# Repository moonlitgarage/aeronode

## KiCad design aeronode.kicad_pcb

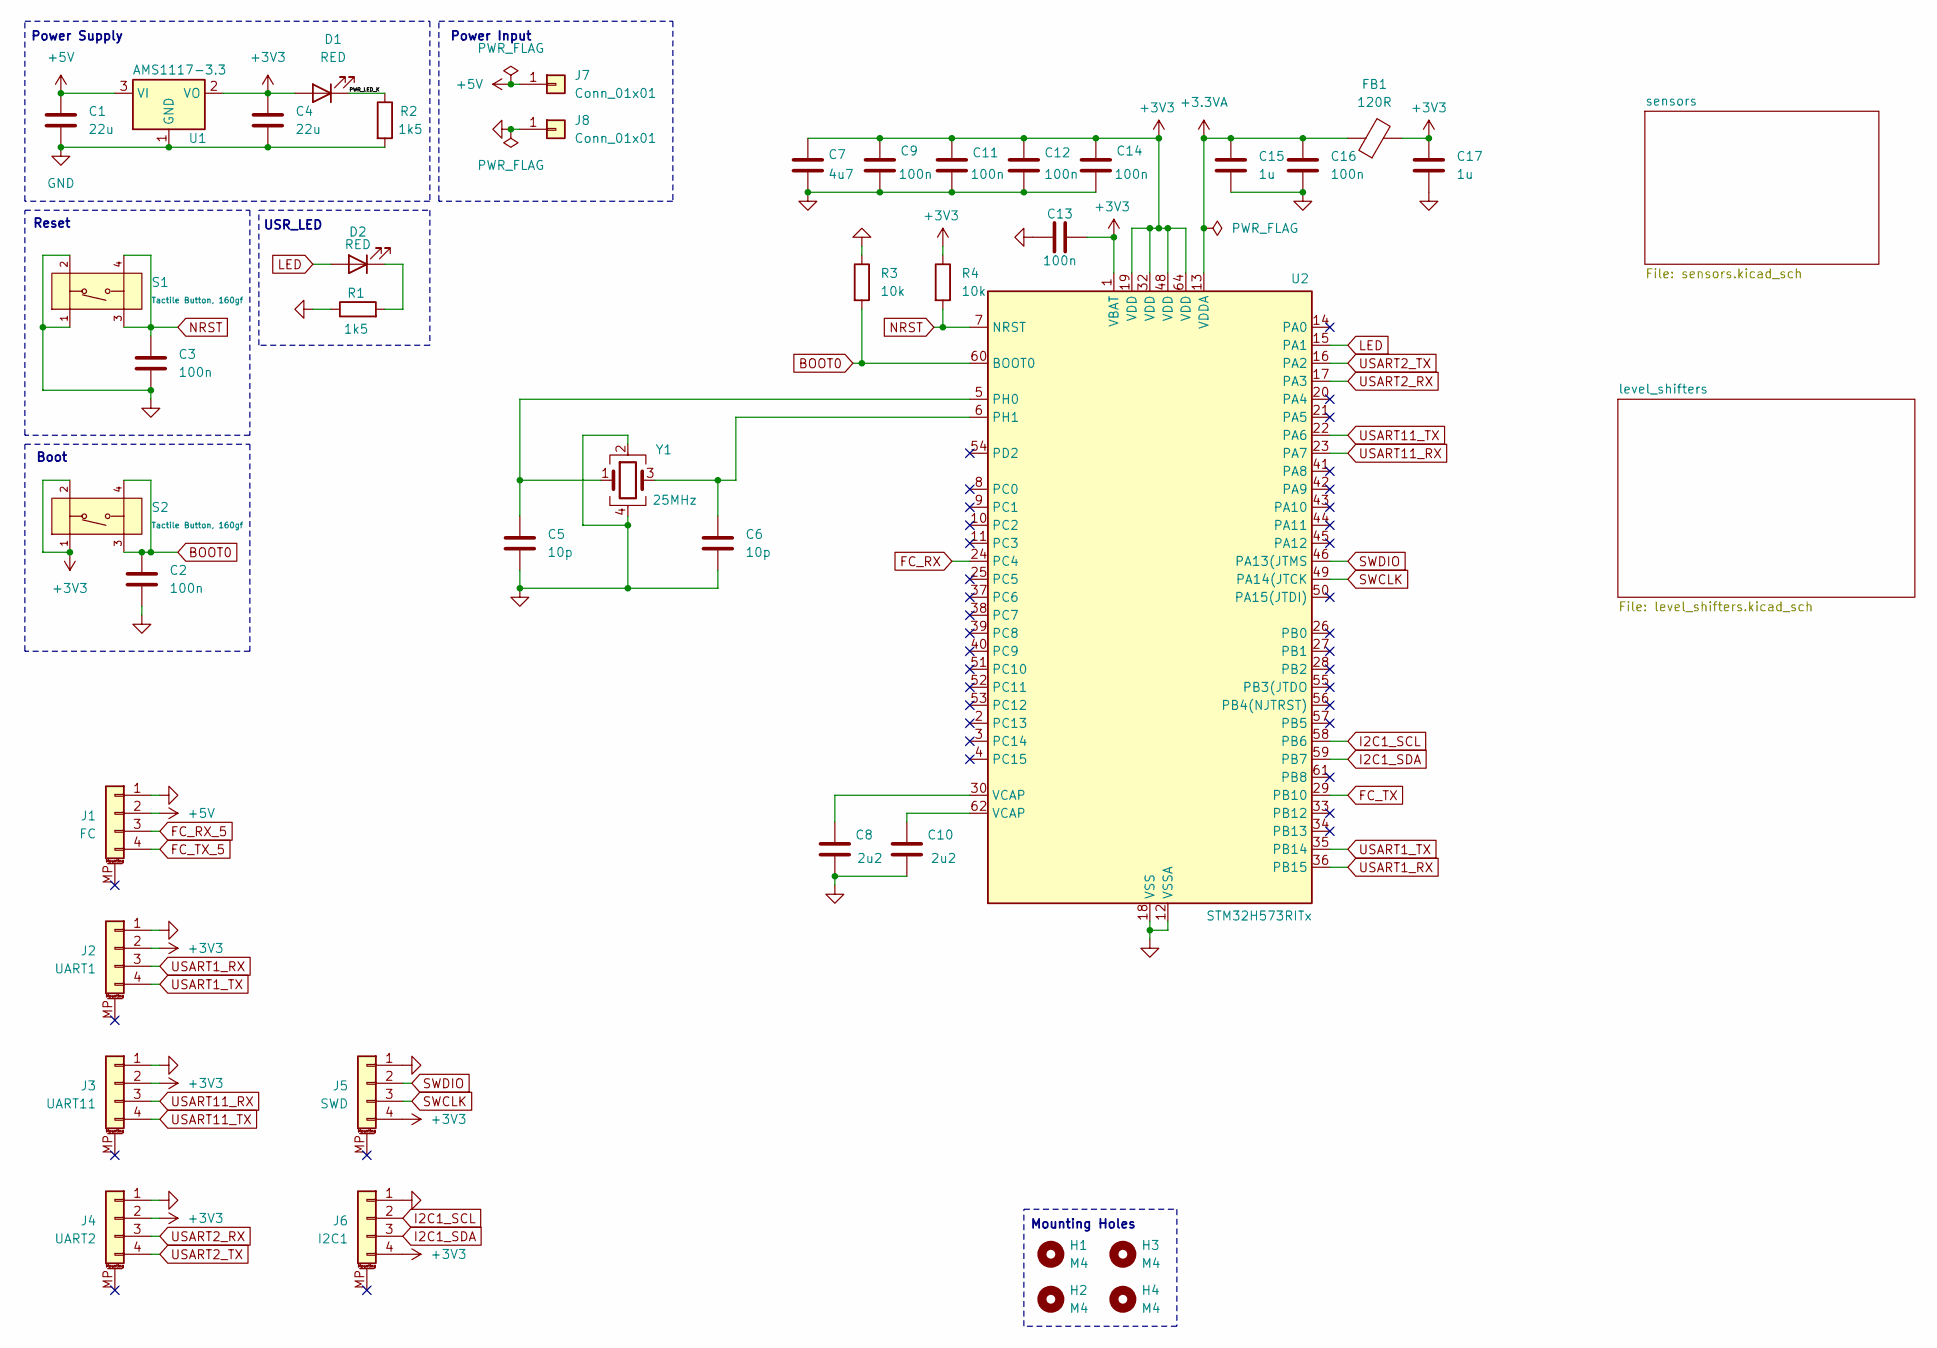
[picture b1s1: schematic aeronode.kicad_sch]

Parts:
C1, C4: 22u; C_0805_2012Metric
C2, C3, C9, C11, C12, C13, C14, C16: 100n; C_0402_1005Metric
C5, C6: 10p; C_0402_1005Metric
C7: 4u7; C_0603_1608Metric
C8, C10: 2u2; C_0402_1005Metric
C15, C17: 1u; C_0402_1005Metric
D1, D2: RED; LED_0603_1608Metric
FB1: 120R; L_0603_1608Metric
H1, H2, H3, H4: M4; MountingHole_4.3mm_M4
J1: FC; JST_GH_SM04B-GHS-TB_1x04-1MP_P1.25mm_Horizontal
J2: UART1; JST_GH_SM04B-GHS-TB_1x04-1MP_P1.25mm_Horizontal
J3: UART11; JST_GH_SM04B-GHS-TB_1x04-1MP_P1.25mm_Horizontal
J4: UART2; JST_GH_SM04B-GHS-TB_1x04-1MP_P1.25mm_Horizontal
J5: SWD; JST_GH_SM04B-GHS-TB_1x04-1MP_P1.25mm_Horizontal
J6: I2C1; JST_GH_SM04B-GHS-TB_1x04-1MP_P1.25mm_Horizontal
J7, J8: Conn_01x01; SolderWirePad_1x01_SMD_2x4mm
R1, R2: 1k5; R_0402_1005Metric
R3, R4: 10k; R_0402_1005Metric
S1, S2: Tactile Button, 160gf; SW-SMD_4P-L5.1-W5.1-P3.70-LS6.5-TL-2; Voltage Rating (Dc) 12V; Part TS-1187A-B-A-B; LCSC C318884
U1: AMS1117-3.3; SOT-223-3_TabPin2
U2: STM32H573RITx; LQFP-64_10x10mm_P0.5mm
Y1: 25MHz; Crystal_SMD_3225-4Pin_3.2x2.5mm

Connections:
+3.3VA: C15.2, C16.2, FB1.1, U2.13 (VDDA)
+3V3: C4.1, C7.1, C9.1, C11.1, C12.1, C13.2, C14.1, C17.2, D1.2 (A), FB1.2, J2.2, J3.2, J4.2, J5.4, J6.4, R4.1, S2.1 (A), S2.2 (B), U1.2 (VO), U2.1 (VBAT), U2.19 (VDD), U2.32 (VDD), U2.48 (VDD), U2.64 (VDD); also elsewhere on the board
+5V: C1.1, J1.2, J7.1, U1.3 (VI); also elsewhere on the board
/PWR_LED_K: D1.1 (K), R2.1
BOOT0: C2.1, R3.2, S2.3 (C), S2.4 (D), U2.60 (BOOT0)
FC_RX: U2.24 (PC4); also elsewhere on the board
FC_RX_5: J1.3; also elsewhere on the board
FC_TX: U2.29 (PB10); also elsewhere on the board
FC_TX_5: J1.4; also elsewhere on the board
GND: C1.2, C2.2, C3.2, C4.2, C5.2, C6.2, C7.2, C8.2, C9.2, C10.2, C11.2, C12.2, C13.1, C14.2, C15.1, C16.1, C17.1, J1.1, J2.1, J3.1, J4.1, J5.1, J6.1, J8.1, R1.1, R2.2, R3.1, S1.1 (A), S1.2 (B), U1.1 (GND), U2.12 (VSSA), U2.18 (VSS), U2.31 (VSS), U2.47 (VSS), U2.63 (VSS), Y1.2, Y1.4; also elsewhere on the board
I2C1_SCL: J6.2, U2.58 (PB6); also elsewhere on the board
I2C1_SDA: J6.3, U2.59 (PB7); also elsewhere on the board
LED: D2.2 (A), U2.15 (PA1)
NRST: C3.1, R4.2, S1.3 (C), S1.4 (D), U2.7 (NRST)
unnamed: C8.1, U2.30 (VCAP)
unnamed: C10.1, U2.62 (VCAP)
unnamed: D2.1 (K), R1.2
unnamed: C5.1, U2.5 (PH0), Y1.1
unnamed: C6.1, U2.6 (PH1), Y1.3
SWCLK: J5.3, U2.49 (PA14(JTCK)
SWDIO: J5.2, U2.46 (PA13(JTMS)
USART1_RX: J2.3, U2.36 (PB15)
USART1_TX: J2.4, U2.35 (PB14)
USART2_RX: J4.3, U2.17 (PA3)
USART2_TX: J4.4, U2.16 (PA2)
USART11_RX: J3.3, U2.23 (PA7)
USART11_TX: J3.4, U2.22 (PA6)

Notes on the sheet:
Power Input
Power Supply
USR_LED
Mounting Holes
Reset
Boot

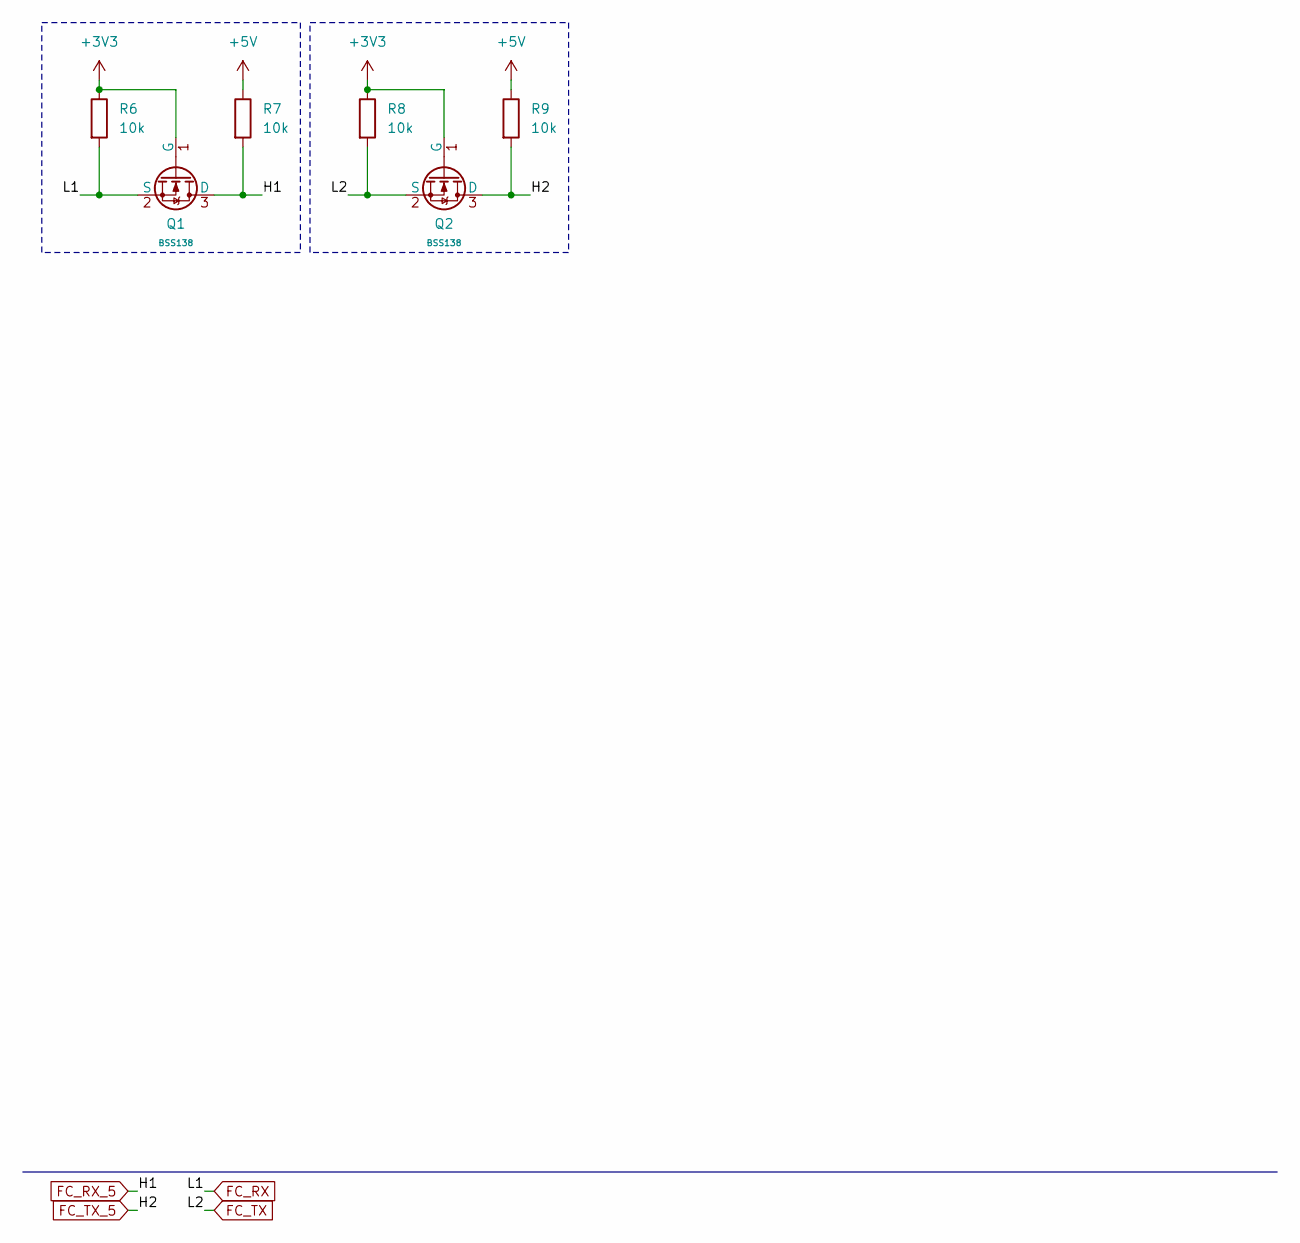
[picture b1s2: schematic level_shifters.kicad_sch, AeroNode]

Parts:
Q1, Q2: BSS138; Q_SOT-23; Part BSS138; LCSC C7420339
R6, R7, R8, R9: 10k; R_0402_1005Metric

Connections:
+3V3: Q1.1 (G), Q2.1 (G), R6.1, R8.1; also elsewhere on the board
+5V: R7.1, R9.1; also elsewhere on the board
FC_RX: Q1.2 (S), R6.2; also elsewhere on the board
FC_RX_5: Q1.3 (D), R7.2; also elsewhere on the board
FC_TX: Q2.2 (S), R8.2; also elsewhere on the board
FC_TX_5: Q2.3 (D), R9.2; also elsewhere on the board

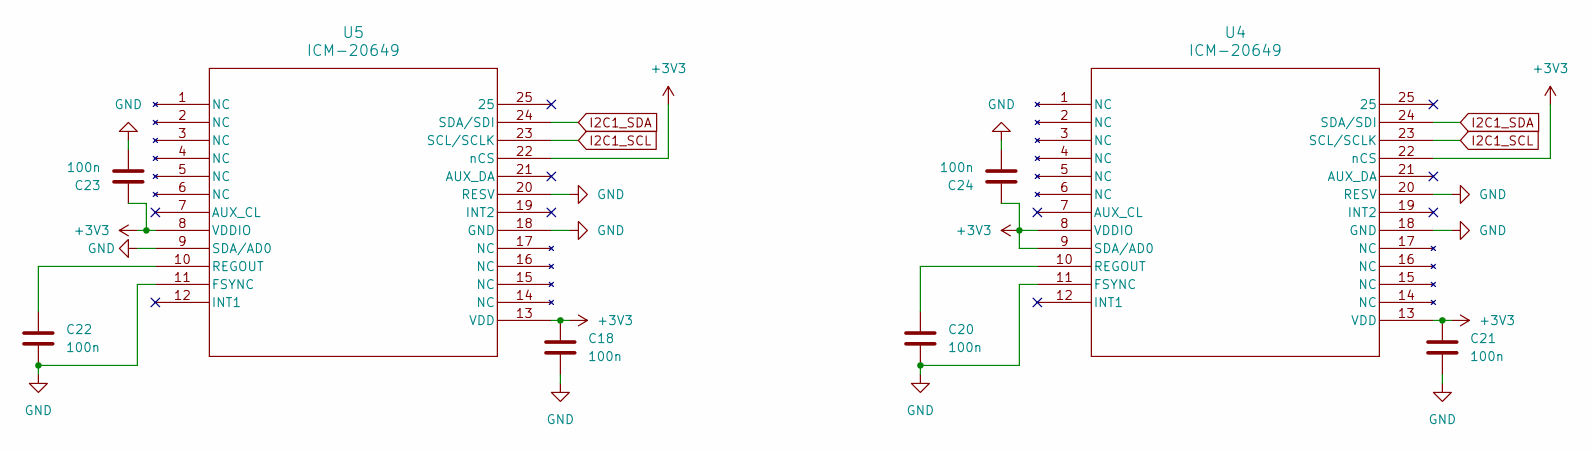
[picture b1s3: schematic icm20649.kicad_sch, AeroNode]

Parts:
C18, C20, C21, C22, C23, C24: 100n; C_0402_1005Metric
U4, U5: ICM-20649; QFN24_3X3X0P9_IVS

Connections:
+3V3: C18.1, C21.1, C23.1, C24.1, U4.8 (VDDIO), U4.9 (SDA/AD0), U4.13 (VDD), U4.22 (nCS), U5.8 (VDDIO), U5.13 (VDD), U5.22 (nCS); also elsewhere on the board
GND: C18.2, C20.2, C21.2, C22.2, C23.2, C24.2, U4.11 (FSYNC), U4.18 (GND), U4.20 (RESV), U5.9 (SDA/AD0), U5.11 (FSYNC), U5.18 (GND), U5.20 (RESV); also elsewhere on the board
I2C1_SCL: U4.23 (SCL/SCLK), U5.23 (SCL/SCLK); also elsewhere on the board
I2C1_SDA: U4.24 (SDA/SDI), U5.24 (SDA/SDI); also elsewhere on the board
unnamed: C20.1, U4.10 (REGOUT)
unnamed: C22.1, U5.10 (REGOUT)

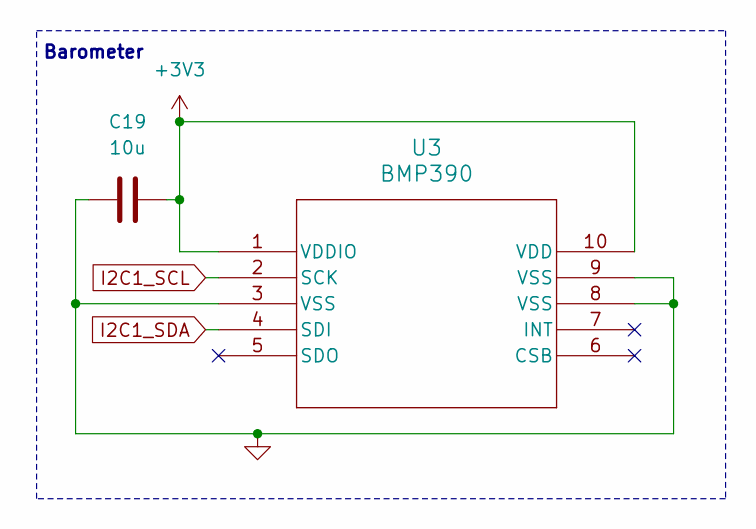
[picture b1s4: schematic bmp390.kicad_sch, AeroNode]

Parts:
C19: 10u; C_0402_1005Metric
U3: BMP390; 10LGA_2X2X0p75_BOS

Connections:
+3V3: C19.1, U3.1 (VDDIO), U3.10 (VDD); also elsewhere on the board
GND: C19.2, U3.3 (VSS), U3.8 (VSS), U3.9 (VSS); also elsewhere on the board
I2C1_SCL: U3.2 (SCK); also elsewhere on the board
I2C1_SDA: U3.4 (SDI); also elsewhere on the board

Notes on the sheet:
Barometer

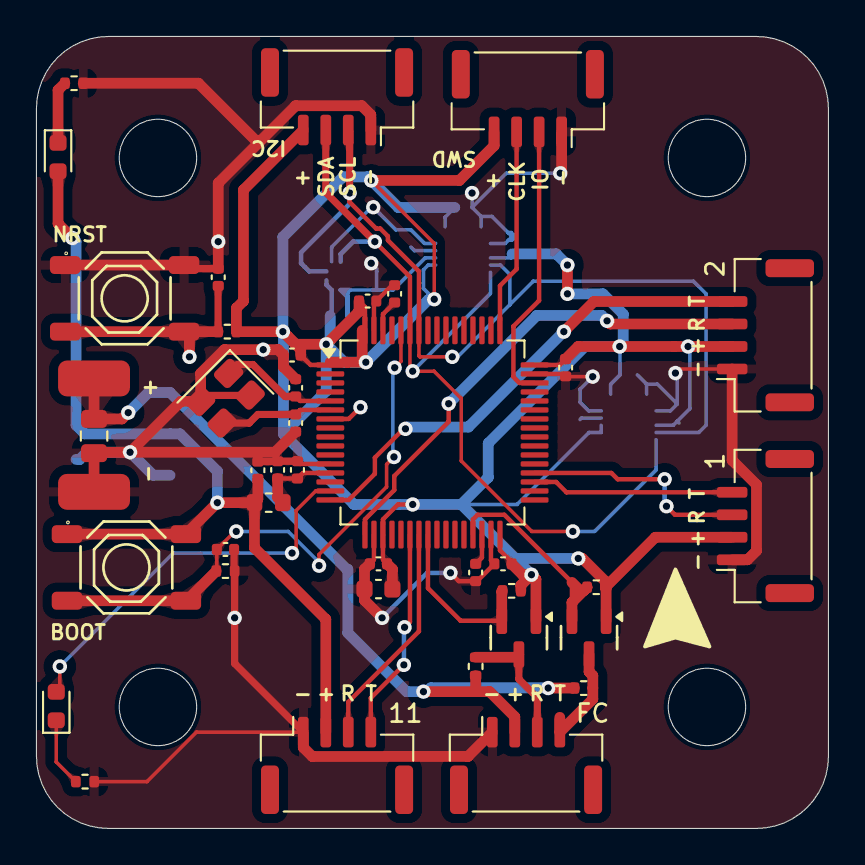
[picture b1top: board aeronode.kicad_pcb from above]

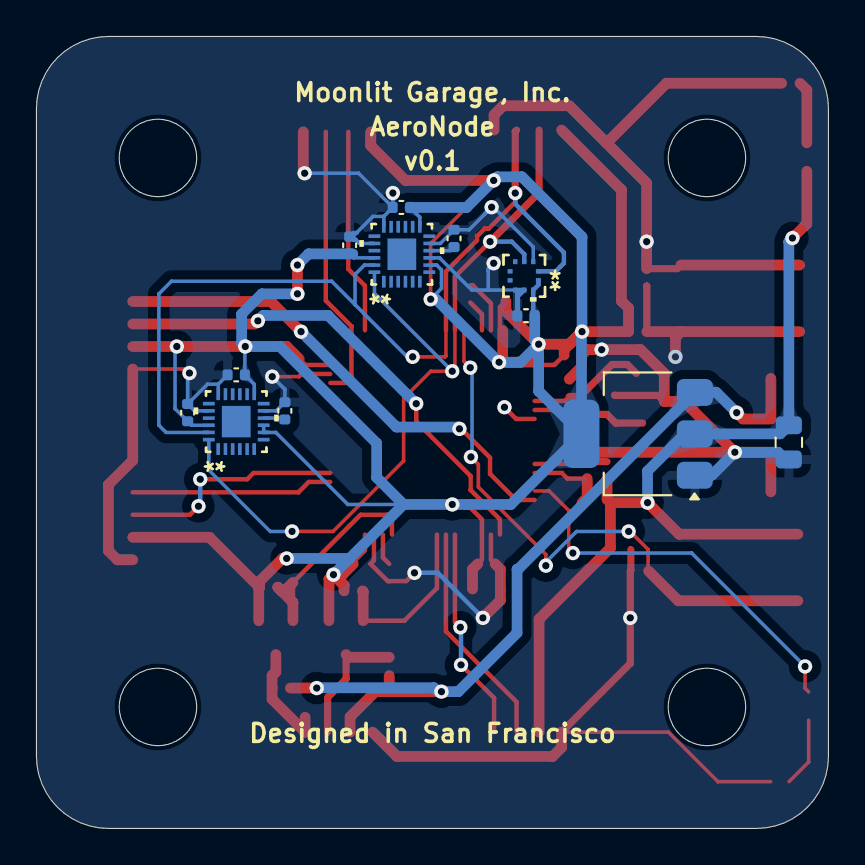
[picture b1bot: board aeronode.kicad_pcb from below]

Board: 4 copper layers, 44.0 x 44.0 mm, 57 parts (12 on the bottom side), 29 nets.

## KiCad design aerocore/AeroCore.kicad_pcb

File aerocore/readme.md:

# aerocore
## components
| Type | ID | I2C | SPI | Datasheet | Product Link | Optional |
| :---: | :---: | :---: | :---: | :---: | :---: | :---: |
| Accel + Gyro | BMI088 | Y | Y | [mouser](https://www.mouser.com/datasheet/2/783/BST_BMI088_DS001-1509549.pdf) | [mouser](https://www.mouser.com/ProductDetail/262-BMI088) | N |
| Magnetometer | LIS3MDLTR | Y | Y | [mouser](https://www.mouser.com/datasheet/2/389/lis3mdl-1849592.pdf) | [mouser](https://www.mouser.com/ProductDetail/STMicroelectronics/LIS3MDLTR?qs=hnsWAVXnr6EbLE48dGN9Pg%3D%3D) | N |
| Pressure + Temp | BMP390 | Y | Y | [mouser](https://www.mouser.com/datasheet/2/783/bst_bmp390_ds002-2448819.pdf) | [mouser](https://www.mouser.com/ProductDetail/Bosch-Sensortec/BMP390?qs=QNEnbhJQKvYQVfvRMgo2YA%3D%3D) | N |
| LoRa | RFM95W | - | Y | [mouser](https://www.mouser.com/datasheet/2/975/1463993415RFM95_96_97_98W-1858106.pdf) / [hoperf](https://www.hoperf.com/uploads/RFM96W-V2.0_1695351477.pdf) | [mouser](https://www.mouser.com/ProductDetail/RF-Solutions/RFM95W-868S2?qs=sGAEpiMZZMu3sxpa5v1qriuzrjO9DfPi5Wv3OoHC154%3D) | Y |
| MCU | RP2040  | - | - | [raspberrypi](https://datasheets.raspberrypi.com/rp2040/rp2040-datasheet.pdf) | [raspberrypi](https://www.raspberrypi.com/documentation/microcontrollers/rp2040.html) | N |

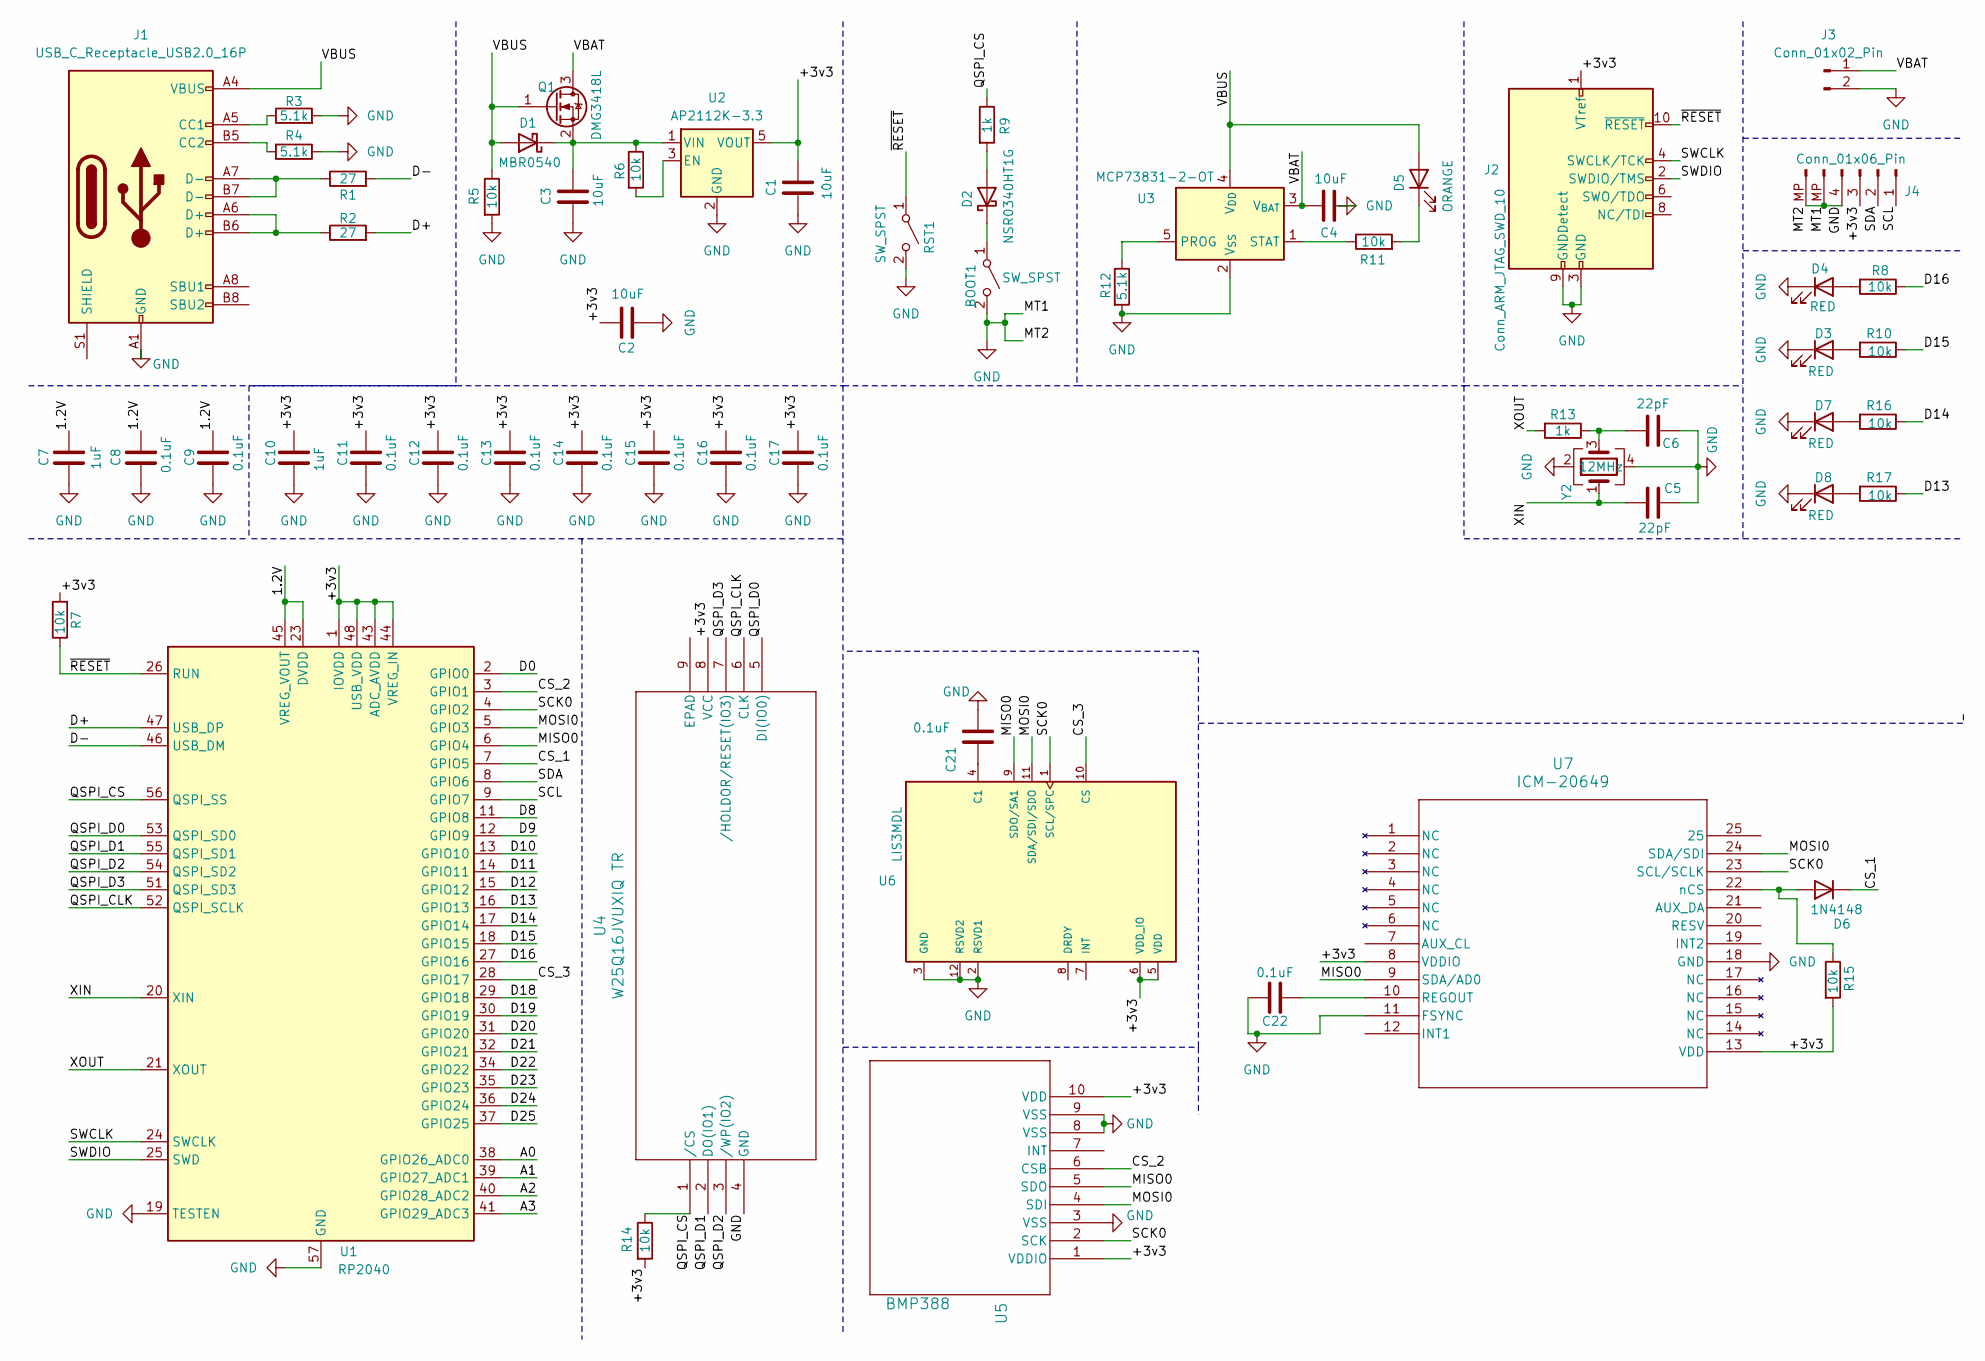
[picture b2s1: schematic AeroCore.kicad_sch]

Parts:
BOOT1: SW_SPST; SW_Push_1P1T_NO_CK_KMR2
C1, C2, C3, C4: 10uF; C_0805_2012Metric_Pad1.18x1.45mm_HandSolder
C5, C6: 22pF; C_0805_2012Metric_Pad1.18x1.45mm_HandSolder
C7, C10: 1uF; C_0603_1608Metric_Pad1.08x0.95mm_HandSolder
C8, C9, C11, C12, C13, C14, C15, C16, C17, C21, C22: 0.1uF; C_0603_1608Metric_Pad1.08x0.95mm_HandSolder
D1: MBR0540; D_SOD-123
D2: NSR0340HT1G; D_SOD-323
D3, D4, D7, D8: RED; LED_0603_1608Metric_Pad1.05x0.95mm_HandSolder
D5: ORANGE; LED_0603_1608Metric_Pad1.05x0.95mm_HandSolder
D6: 1N4148; D_DO-35_SOD27_P7.62mm_Horizontal
J1: USB_C_Receptacle_USB2.0_16P; USB_C_Receptacle_Palconn_UTC16-G
J2: Conn_ARM_JTAG_SWD_10; PinSocket_2x05_P1.27mm_Vertical_SMD
J3: Conn_01x02_Pin; JST_EH_S2B-EH_1x02_P2.50mm_Horizontal
J4: Conn_01x06_Pin; JST_SH_SM04B-SRSS-TB_1x04-1MP_P1.00mm_Horizontal
Q1: DMG3418L; SOT-23
R1, R2: 27; R_0603_1608Metric_Pad0.98x0.95mm_HandSolder
R3, R4, R12: 5.1k; R_0603_1608Metric_Pad0.98x0.95mm_HandSolder
R5, R6, R7, R8, R10, R11, R14, R15, R16, R17: 10k; R_0603_1608Metric_Pad0.98x0.95mm_HandSolder
R9, R13: 1k; R_0603_1608Metric_Pad0.98x0.95mm_HandSolder
RST1: SW_SPST; SW_Push_1P1T_NO_CK_KMR2
U1: RP2040; QFN-56-1EP_7x7mm_P0.4mm_EP3.2x3.2mm
U2: AP2112K-3.3; SOT-23-5
U3: MCP73831-2-OT; SOT-23-5
U4: W25Q16JVUXIQ TR; Winbond_USON-8-1EP_3x2mm_P0.5mm_EP0.2x1.6mm
U5: BMP388; SENSORM-SMD_BMP388
U6: LIS3MDL; LGA-12_L2.0-W2.0-P0.50-BL; PARTREV 6
U7: ICM-20649; QFN-24_L3.0-W3.0-P0.40-TL-EP1.4
Y2: 12MHz; Crystal_SMD_2520-4Pin_2.5x2.0mm

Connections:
/1.2V: C7.1, C8.1, C9.1, U1.23 (DVDD), U1.45 (VREG_VOUT), U1.50 (DVDD)
/+3v3: C1.1, C2.1, C10.1, C11.1, C12.1, C13.1, C14.1, C15.1, C16.1, C17.1, J2.1 (VTref), J4.3, R7.2, R14.2, R15.2, U1.1 (IOVDD), U1.10 (IOVDD), U1.22 (IOVDD), U1.33 (IOVDD), U1.42 (IOVDD), U1.43 (ADC_AVDD), U1.44 (VREG_IN), U1.48 (USB_VDD), U1.49 (IOVDD), U2.5 (VOUT), U4.8 (VCC), U5.1 (VDDIO), U5.10 (VDD), U6.5 (VDD), U6.6 (VDD_IO), U7.8 (VDDIO), U7.13 (VDD)
/A0: U1.38 (GPIO26_ADC0)
/A1: U1.39 (GPIO27_ADC1)
/A2: U1.40 (GPIO28_ADC2)
/A3: U1.41 (GPIO29_ADC3)
/CS_1: D6.1 (K), U1.7 (GPIO5)
/CS_2: U1.3 (GPIO1), U5.6 (CSB)
/CS_3: U1.28 (GPIO17), U6.10 (CS)
/D0: U1.2 (GPIO0)
/D8: U1.11 (GPIO8)
/D9: U1.12 (GPIO9)
/D10: U1.13 (GPIO10)
/D11: U1.14 (GPIO11)
/D12: U1.15 (GPIO12)
/D13: R17.1, U1.16 (GPIO13)
/D14: R16.1, U1.17 (GPIO14)
/D15: R10.1, U1.18 (GPIO15)
/D16: R8.1, U1.27 (GPIO16)
/D18: U1.29 (GPIO18)
/D19: U1.30 (GPIO19)
/D20: U1.31 (GPIO20)
/D21: U1.32 (GPIO21)
/D22: U1.34 (GPIO22)
/D23: U1.35 (GPIO23)
/D24: U1.36 (GPIO24)
/D25: U1.37 (GPIO25)
/D+: R2.2, U1.47 (USB_DP)
/D-: R1.2, U1.46 (USB_DM)
/MISO0: U1.6 (GPIO4), U5.5 (SDO), U6.9 (SDO/SA1), U7.9 (SDA/AD0)
/MOSI0: U1.5 (GPIO3), U5.4 (SDI), U6.11 (SDA/SDI/SDO), U7.24 (SDA/SDI)
/QSPI_CLK: U1.52 (QSPI_SCLK), U4.6 (CLK)
/QSPI_CS: R9.1, R14.1, U1.56 (QSPI_SS), U4.1 (/CS)
/QSPI_D0: U1.53 (QSPI_SD0), U4.5 (DI(IO0))
/QSPI_D1: U1.55 (QSPI_SD1), U4.2 (DO(IO1))
/QSPI_D2: U1.54 (QSPI_SD2), U4.3 (/WP(IO2))
/QSPI_D3: U1.51 (QSPI_SD3), U4.7 (/HOLDOR/RESET(IO3))
/SCK0: U1.4 (GPIO2), U5.2 (SCK), U6.1 (SCL/SPC), U7.23 (SCL/SCLK)
/SCL: J4.1, U1.9 (GPIO7)
/SDA: J4.2, U1.8 (GPIO6)
/SWCLK: J2.4 (SWCLK/TCK), U1.24 (SWCLK)
/SWDIO: J2.2 (SWDIO/TMS), U1.25 (SWD)
/VBAT: C4.1, J3.1, Q1.3 (D), U3.3 (V_{BAT})
/VBUS: D1.2 (A), D5.2 (A), J1.A4 (VBUS), J1.A9 (VBUS), J1.B4 (VBUS), J1.B9 (VBUS), Q1.1 (G), R5.1, U3.4 (V_{DD})
/XIN: C5.2, U1.20 (XIN), Y2.1
/XOUT: R13.2, U1.21 (XOUT)
/~RESET: J2.10 (~RESET), R7.1, RST1.1 (A), U1.26 (RUN)
GND: BOOT1.2 (B), C1.2, C2.2, C3.2, C4.2, C5.1, C6.1, C7.2, C8.2, C9.2, C10.2, C11.2, C12.2, C13.2, C14.2, C15.2, C16.2, C17.2, C21.2, C22.1, D3.1 (K), D4.1 (K), D7.1 (K), D8.1 (K), J1.A1 (GND), J1.A12 (GND), J1.B1 (GND), J1.B12 (GND), J2.3 (GND), J2.5 (GND), J2.9 (GNDDetect), J3.2, J4.4, J4.MP (Pin_5), R3.2, R4.1, R5.2, R12.2, RST1.2 (B), U1.19 (TESTEN), U1.57 (GND), U2.2 (GND), U3.2 (V_{SS}), U4.4 (GND), U5.3 (VSS), U5.8 (VSS), U5.9 (VSS), U6.2 (RSVD1), U6.3 (GND), U6.12 (RSVD2), U7.11 (FSYNC), U7.18 (GND), Y2.2, Y2.4
unnamed: BOOT1.1 (A), D2.1 (K)
unnamed: C6.2, R13.1, Y2.3
unnamed: C3.1, D1.1 (K), Q1.2 (S), R6.1, U2.1 (VIN)
unnamed: D2.2 (A), R9.2
unnamed: D3.2 (A), R10.2
unnamed: D4.2 (A), R8.2
unnamed: D5.1 (K), R11.2
unnamed: D6.2 (A), R15.1, U7.22 (nCS)
unnamed: D7.2 (A), R16.2
unnamed: D8.2 (A), R17.2
unnamed: J1.A5 (CC1), R3.1
unnamed: J1.B5 (CC2), R4.2
unnamed: J1.A6 (D+), J1.B6 (D+), R2.1
unnamed: J1.A7 (D-), J1.B7 (D-), R1.1
unnamed: R6.2, U2.3 (EN)
unnamed: R12.1, U3.5 (PROG)
unnamed: R11.1, U3.1 (STAT)
unnamed: C21.1, U6.4 (C1)
unnamed: C22.2, U7.10 (REGOUT)

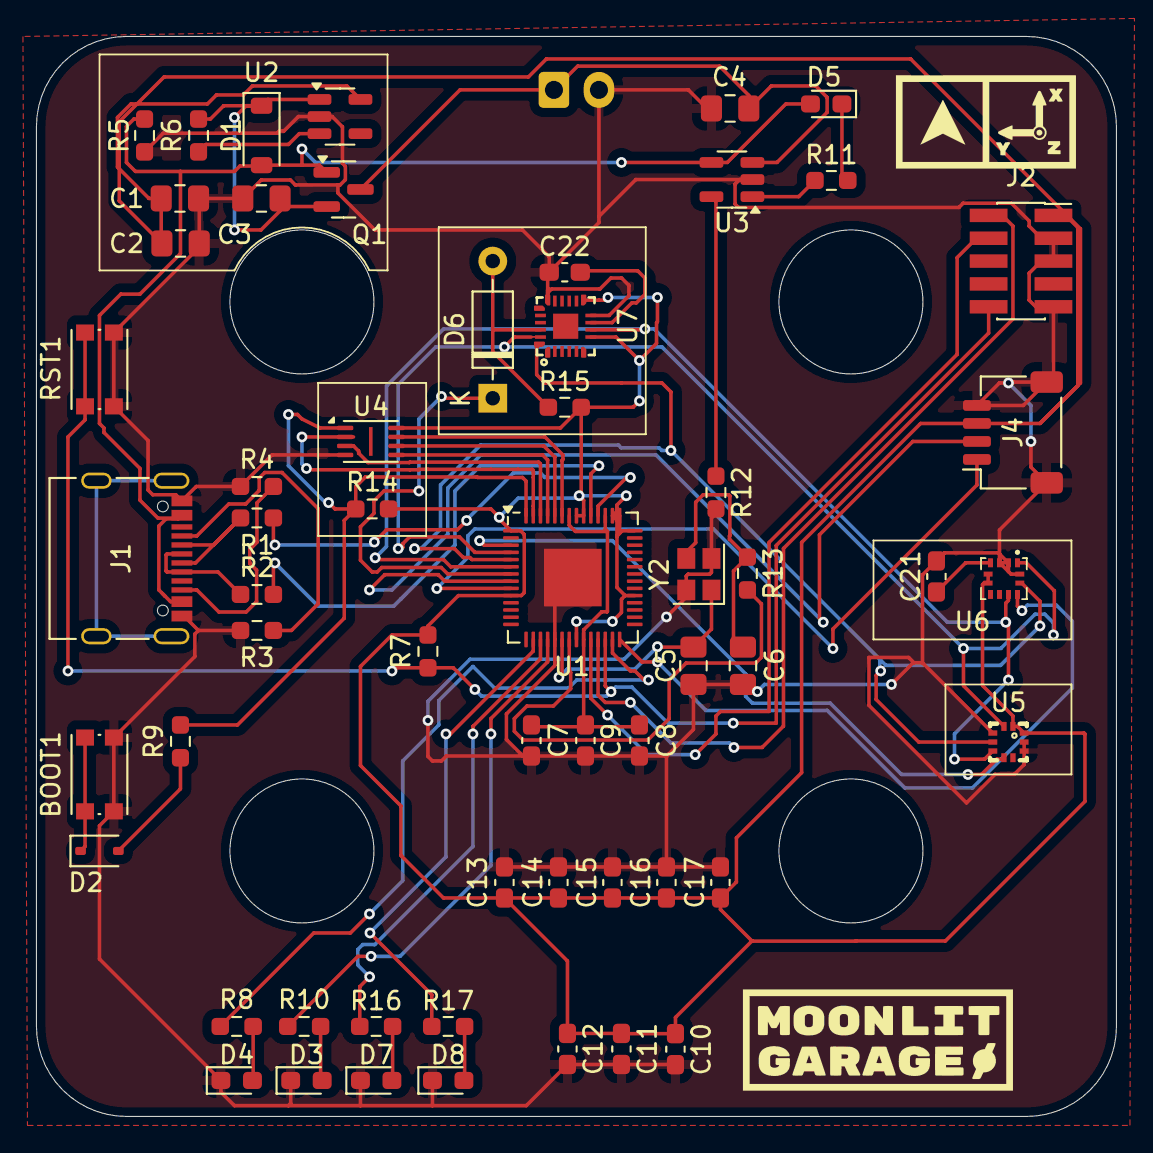
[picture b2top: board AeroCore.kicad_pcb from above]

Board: 2 copper layers, 60.0 x 60.0 mm, 59 parts (1 on the bottom side), 49 nets.

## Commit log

2024-06-15 add website
2024-06-15 add firmware
2024-06-15 add aerocore
2024-06-15 add docs
2024-06-15 update links
2024-06-15 add new logo
2024-06-17 add metadata for publishing
2024-06-17 rename aeronode to aeroapi
2024-06-17 bump version
2024-06-22 add board v0.1.0
2024-06-24 add dashed borders
2024-06-24 remove redundant readme badge
2024-06-27 add abstracted rp2040 impl
2024-06-29 update docs links
2024-07-04 start hil simulation docs
2024-07-07 add firmware and pcb
2024-07-07 add instagram link
2024-07-07 change name
2024-07-13 refactor echo code
2024-07-13 add aerobridge code
2024-07-15 add channel based control inputs
2024-07-16 get rpc working
2024-07-16 add rpc code
2024-07-16 add rust
2024-07-17 add rust to python rpc
2024-07-17 update for rp-pico
2024-07-17 remove python client
2024-07-17 add tui
2024-07-18 add tokio to run tui and rpc at same time
2024-07-18 rename landing website
2024-07-18 make separate directory for all websites
2024-07-19 change waitlist form to loops
2024-07-19 remove redundant import
2024-07-19 update waitlist text
2024-07-19 add toasts for waitlist response
2024-07-22 add spi control
2024-07-22 add bmp380 read code
2024-07-23 add datatypes
2024-07-23 refactor code
2024-07-23 add pycapnp
2024-07-23 change types
2024-07-23 add serial connection and selction switch
2024-07-24 add nested layout
2024-07-24 add custom widgets for instruments and controls
2024-07-24 add gradual changes to flight control
2024-07-26 add new path for shikanoko meme
2024-07-27 add datasheet links
2024-07-27 update data format
2024-07-28 make custom rp2040 based design
2024-08-01 add sensors to schematics
2024-08-02 update info for lis3mdltr
2024-08-02 use newer sensor for accel and gyro
2024-08-02 update link for lora
2024-08-02 change mcu
2024-08-02 add pcb for old design
2024-08-02 update packages
2024-08-03 add 3d model on website
2024-08-03 fix threejs import path
2024-08-04 add optional components
2024-08-06 keep rp2040 as mcu
2024-09-05 add files for final board
2024-09-23 update pcb schematic
2024-10-01 update links to point to moonlitgarage
2024-10-02 update footer
2024-10-02 remove .DS_Store
2024-10-02 move websites to separate repo
2024-10-02 init foxtrot
2024-11-01 move aerobridge to https://github.com/moonlitgarage/aerobridge
2025-01-03 remove firmware and docs
2025-04-14 add v0 design
2025-07-20 backup commit
2026-01-02 v0.1
2026-01-10 clean slate
